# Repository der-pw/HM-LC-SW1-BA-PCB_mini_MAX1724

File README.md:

# AskSin++ Batterieaktor mit MAX1724 Stepup

**HM-LC-SW1-BA-PCB_mini mit einer Ausgangsspannung von 3,3V, bspw. für Mini-Lichterketten.**

* [Sketch](./Sketch/HM-LC-SW1-BA-PCB_extBatt.ino)
* [Gehäuse](./Case/)
* [Teileliste](./HM-LC-SW1-BA-PCB_mini_MAX1724-Parts.csv)

Der Ausgang wird über einen N-Channel MOSFET geschaltet und kann, je nach Versorgungsspannung, mit bis zu 150mA belastet werden.
Für kleine Mini-Lichterketten ist das ausreichend.
(Beispiel: eine Mini-Lichterkette aus den üblichen Grabbelschütten, mit 10 LEDs und 10Ohm Vorwiderstand benötigt ca 35mA).

**Batterie-Messung:**  
Desweiteren kann die Batteriespannung vor dem Stepup mittels Spannungsteiler gemessen werden. 
Ein angepasster Sketch liegt bei. Vielen Dank an Jérôme für die Unterstützung und das Aufzeigen, wie "einfach" doch die Batterieklasse ist. ;-)

Da in der CCU, bei diesem Aktor, die Batteriemeldung nur im Bereich von 5-15V auslöst, wird im Sketch unter ...
```
uint8_t lowbat = getList0().lowBatLimit() / 5; //factor 5 to get low bat
```
... die eingestellte Batterieschwelle durch 5 geteilt.
In der CCU müssen also die Spannungwerte mit "x5" angegeben werden.
Beispiel: Batteriemeldung bei 2,1V Versorgungsspannung. Heißt 2,1V x 5 = 10,5V. Es müssen demnach 10,5V in der CCU eingestellt werden.
Die Werte variieren je nach verwendetem Batterie.- Akkutyp und müssen "für sich selbst" gefunden werden.

## PCB

Das Platinendesign basiert auf dem [HMSensor](https://github.com/pa-pa/HMSensor/) Projekt.
Weitere Infos zur HMSensor gibt es auf [asksinpp.de](https://asksinpp.de/Projekte/psi/HMSensor/).

## FAQ

* `fatal error: ResetOnBoot.h: No such file or directory`  
  Es ist die aktuellste Version (ggf. master-Branch) der [AskSinPP](https://github.com/pa-pa/AskSinPP) Library zu verwenden

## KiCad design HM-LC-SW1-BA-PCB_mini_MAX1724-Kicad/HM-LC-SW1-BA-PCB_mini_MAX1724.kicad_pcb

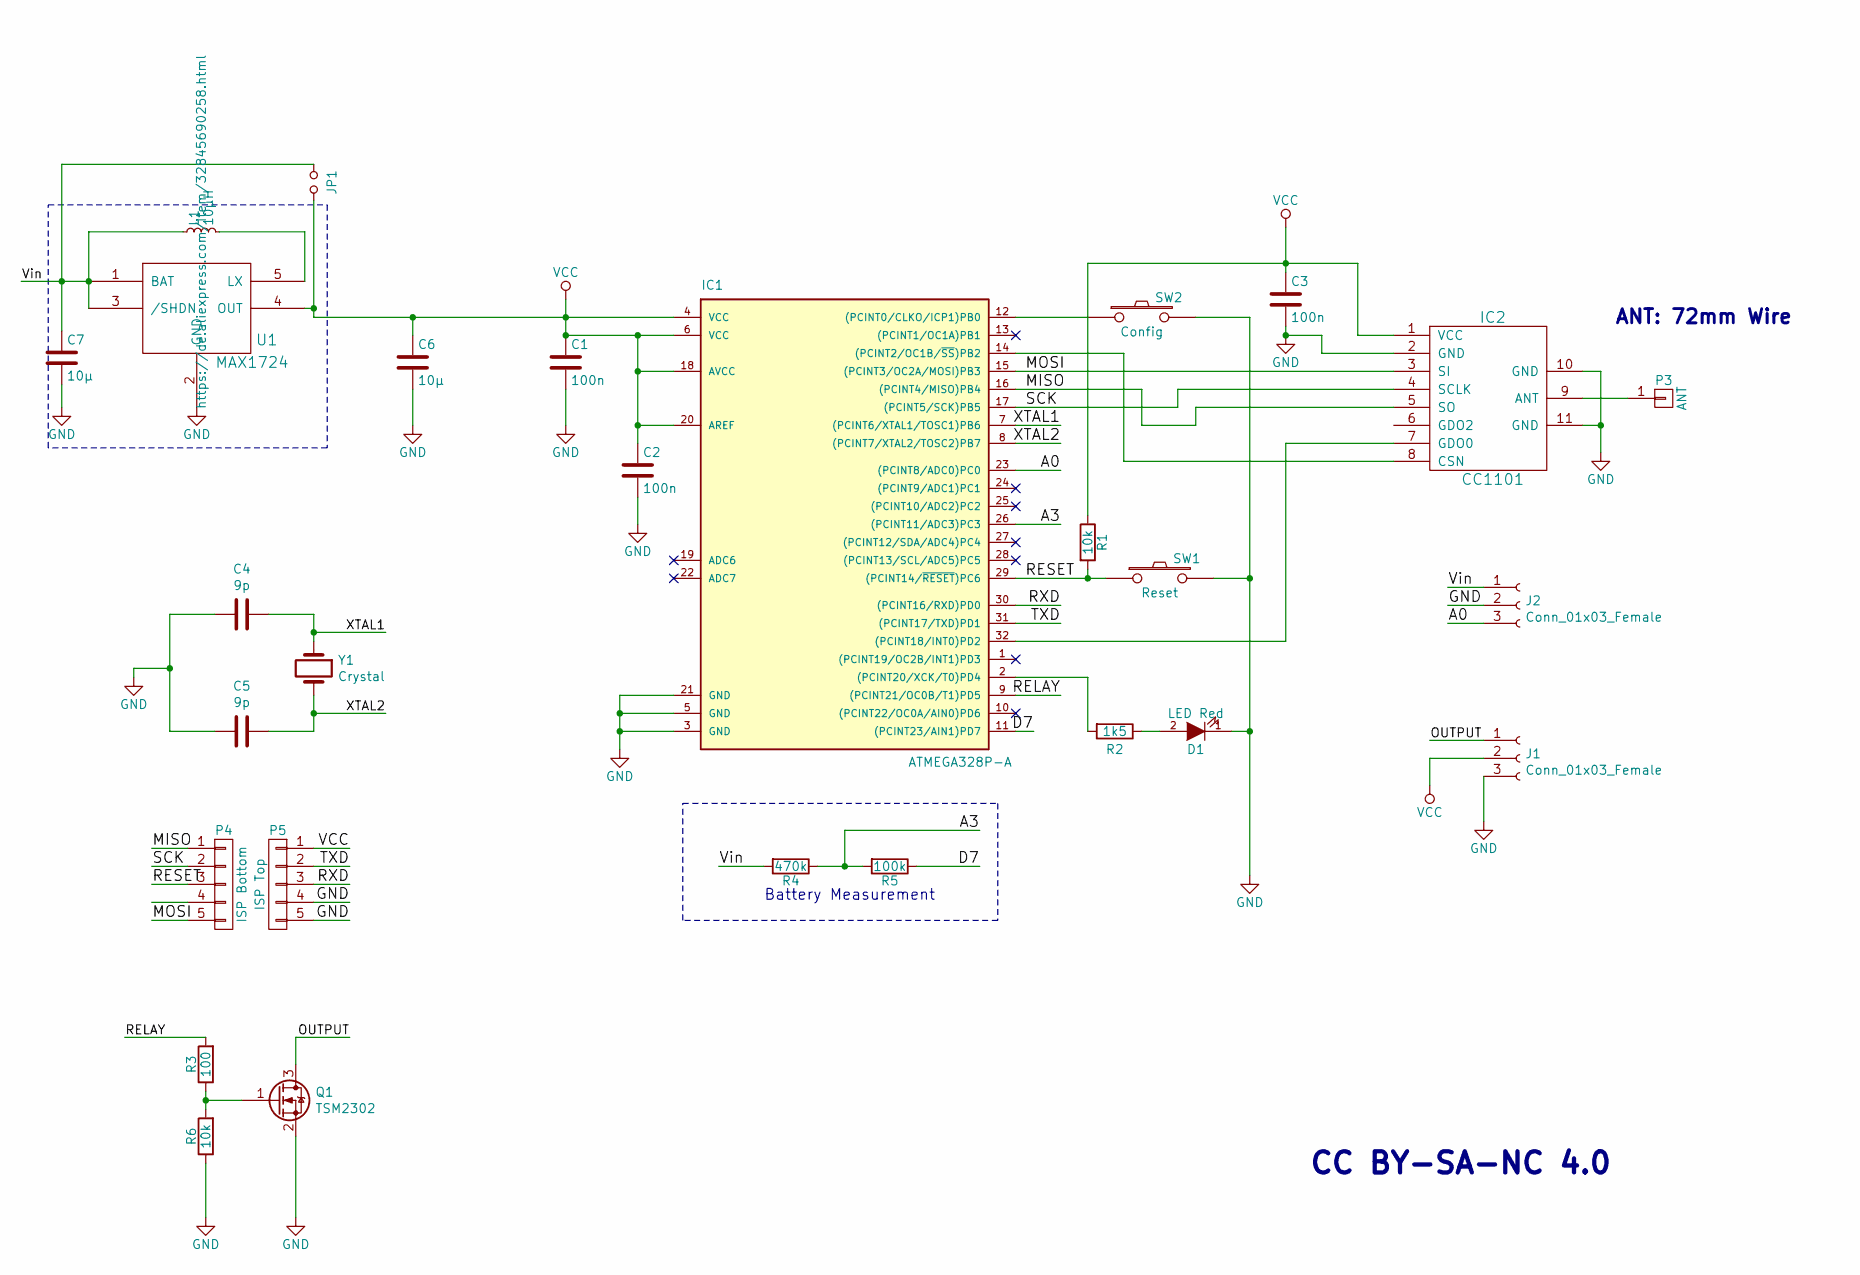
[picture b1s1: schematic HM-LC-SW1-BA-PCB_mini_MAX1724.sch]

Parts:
C1, C2, C3: 100n; C_0805_2012Metric_Pad1.15x1.40mm_HandSolder
C4, C5: 9p; C_0805_2012Metric_Pad1.15x1.40mm_HandSolder
C6, C7: 10µ; C_0805_2012Metric_Pad1.15x1.40mm_HandSolder
D1: LED Red; LED_1206_3216Metric_Pad1.42x1.75mm_HandSolder
IC1: ATMEGA328P-A; TQFP-32_7x7mm_Pitch0.8mm
IC2: CC1101; CC1101_Module
J1, J2: Conn_01x03_Female; PinHeader_1x03_P2.54mm_Vertical
JP1: Jumper_NO_Small; SolderJumper-2_P1.3mm_Open_RoundedPad1.0x1.5mm
L1: 10µH; L_1812_4532Metric_Pad1.30x3.40mm_HandSolder
P3: ANT; Pin_Header_Straight_1x01_Pitch2.00mm
P4: ISP Bottom; Pin_Header_Straight_1x05_Pitch2.54mm_SMD_BySide
P5: ISP Top; Pin_Header_Straight_1x05_Pitch2.54mm_SMD_BySide
Q1: TSM2302; SOT-23
R1: 10k; R_0805_HandSoldering
R2: 1k5; R_0805_2012Metric_Pad1.15x1.40mm_HandSolder
R3: 100; R_0805_2012Metric_Pad1.15x1.40mm_HandSolder
R4: 470k; R_0805_HandSoldering
R5: 100k; R_0805_HandSoldering
R6: 10k; R_0805_2012Metric_Pad1.15x1.40mm_HandSolder
SW1: Reset; SW_SPST_FSMSM
SW2: Config; SW_SPST_FSMSM
U1: MAX1724; TSOT-23-5
Y1: Crystal; Crystal_SMD_MicroCrystal_CC7V-T1A-2Pin_3.2x1.5mm_HandSolder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

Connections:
/A0: IC1.23 ((PCINT8/ADC0)PC0), J2.3
/A3: IC1.26 ((PCINT11/ADC3)PC3), R4.1, R5.2
/D7: IC1.11 ((PCINT23/AIN1)PD7), R5.1
/MISO: IC1.16 ((PCINT4/MISO)PB4), IC2.5 (SO), P4.1
/MOSI: IC1.15 ((PCINT3/OC2A/MOSI)PB3), IC2.3 (SI), P4.5
/OUTPUT: J1.1, Q1.3 (D)
/RELAY: IC1.9 ((PCINT21/OC0B/T1)PD5), R3.2
/RESET: IC1.29 ((PCINT14/~RESET~)PC6), P4.3, R1.2, SW1.1
/RXD: IC1.30 ((PCINT16/RXD)PD0), P5.3
/SCK: IC1.17 ((PCINT5/SCK)PB5), IC2.4 (SCLK), P4.2
/TXD: IC1.31 ((PCINT17/TXD)PD1), P5.2
/Vin: C7.1, J2.1, JP1.1, L1.1, R4.2, U1.1 (BAT), U1.3 (/SHDN)
/XTAL1: C4.1, IC1.7 ((PCINT6/XTAL1/TOSC1)PB6), Y1.1
/XTAL2: C5.1, IC1.8 ((PCINT7/XTAL2/TOSC2)PB7), Y1.2
GND: C1.2, C2.2, C3.2, C4.2, C5.2, C6.2, C7.2, D1.1 (K), IC1.3 (GND), IC1.5 (GND), IC1.21 (GND), IC2.2 (GND), IC2.10 (GND), IC2.11 (GND), J1.3, J2.2, P5.4, P5.5, Q1.2 (S), R6.1, SW1.2, SW2.2, U1.2 (GND)
unnamed: D1.2 (A), R2.1
unnamed: IC1.2 ((PCINT20/XCK/T0)PD4), R2.2
unnamed: IC1.12 ((PCINT0/CLKO/ICP1)PB0), SW2.1
unnamed: IC1.14 ((PCINT2/OC1B/~SS~)PB2), IC2.8 (CSN)
unnamed: IC1.32 ((PCINT18/INT0)PD2), IC2.7 (GDO0)
unnamed: IC2.9 (ANT), P3.1
unnamed: L1.2, U1.5 (LX)
unnamed: Q1.1 (G), R3.1, R6.2
VCC: C1.1, C2.1, C3.1, C6.1, IC1.4 (VCC), IC1.6 (VCC), IC1.18 (AVCC), IC1.20 (AREF), IC2.1 (VCC), J1.2, JP1.2, P5.1, R1.1, U1.4 (OUT)

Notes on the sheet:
Battery Measurement
CC BY-SA-NC 4.0
ANT: 72mm Wire

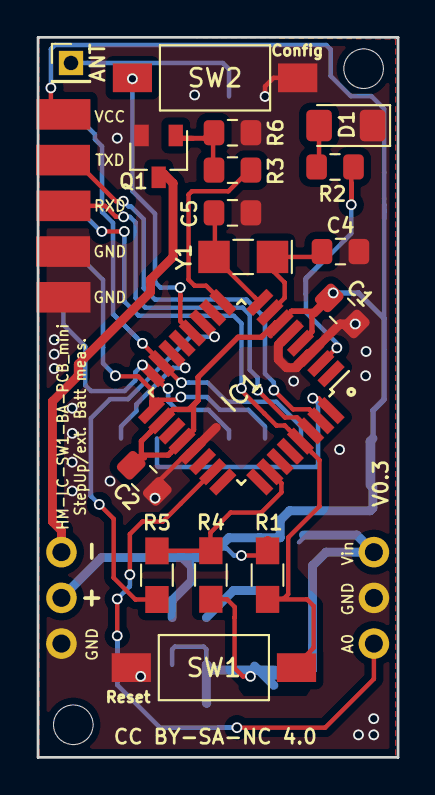
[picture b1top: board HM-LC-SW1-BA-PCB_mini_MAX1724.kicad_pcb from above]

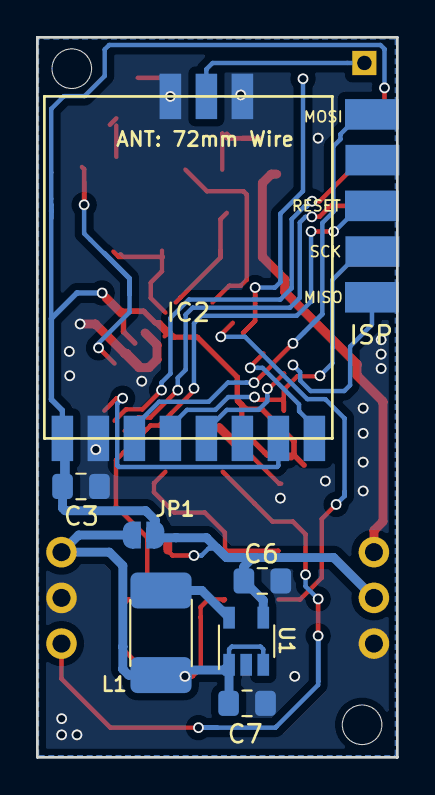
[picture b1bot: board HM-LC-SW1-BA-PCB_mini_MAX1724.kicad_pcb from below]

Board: 2 copper layers, 20.0 x 40.0 mm, 28 parts (8 on the bottom side), 24 nets.

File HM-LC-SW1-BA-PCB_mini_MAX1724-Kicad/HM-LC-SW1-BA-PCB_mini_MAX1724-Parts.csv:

Reference, Quantity, Value, Footprint, Datasheet
C1 C2 C3 ,3,"100n","Capacitor_SMD:C_0805_2012Metric_Pad1.15x1.40mm_HandSolder",""
C4 C5 ,2,"9p","Capacitor_SMD:C_0805_2012Metric_Pad1.15x1.40mm_HandSolder","~"
C6 C7 ,2,"10µ","Capacitor_SMD:C_0805_2012Metric_Pad1.15x1.40mm_HandSolder",""
D1 ,1,"LED Red","LED_SMD:LED_1206_3216Metric_Pad1.42x1.75mm_HandSolder",""
IC1 ,1,"ATMEGA328P-A","Housings_QFP:TQFP-32_7x7mm_Pitch0.8mm",""
IC2 ,1,"CC1101","Modules:CC1101_Module",""
J2 J1 ,2,"Conn_01x03_Female","Connector_PinHeader_2.54mm:PinHeader_1x03_P2.54mm_Vertical","~"
JP1 ,1,"Jumper_NO_Small","Jumper:SolderJumper-2_P1.3mm_Open_RoundedPad1.0x1.5mm",""
L1 ,1,"10µH","Inductor_SMD:L_1812_4532Metric_Pad1.30x3.40mm_HandSolder","https://de.aliexpress.com/item/32845690258.html"
P3 ,1,"ANT","Pin_Headers:Pin_Header_Straight_1x01_Pitch2.00mm",""
P4 ,1,"ISP Bottom","Modules:Pin_Header_Straight_1x05_Pitch2.54mm_SMD_BySide",""
P5 ,1,"ISP Top","Modules:Pin_Header_Straight_1x05_Pitch2.54mm_SMD_BySide",""
Q1 ,1,"TSM2302","Package_TO_SOT_SMD:SOT-23","http://www.farnell.com/datasheets/1945672.pdf"
R1 ,1,"10k","Resistors_SMD:R_0805_HandSoldering",""
R2 ,1,"1k5","Resistor_SMD:R_0805_2012Metric_Pad1.15x1.40mm_HandSolder",""
R3 ,1,"100","Resistor_SMD:R_0805_2012Metric_Pad1.15x1.40mm_HandSolder",""
R4 ,1,"470k","Resistors_SMD:R_0805_HandSoldering",""
R5 ,1,"100k","Resistors_SMD:R_0805_HandSoldering",""
R6 ,1,"10k","Resistor_SMD:R_0805_2012Metric_Pad1.15x1.40mm_HandSolder",""
SW1 ,1,"Reset","Buttons_Switches_SMD:SW_SPST_FSMSM",""
SW2 ,1,"Config","Buttons_Switches_SMD:SW_SPST_FSMSM",""
U1 ,1,"MAX1724","Package_TO_SOT_SMD:TSOT-23-5","https://de.aliexpress.com/item/32353066414.html"
Y1 ,1,"Crystal","Crystal:Crystal_SMD_MicroCrystal_CC7V-T1A-2Pin_3.2x1.5mm_HandSoldering","https://www.reichelt.de/uhrenquarz-keramikgeh-1-5x3-2x0-9mm-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"

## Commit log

2019-11-23 initial
2019-11-23 gerber upload
2019-11-23 order structure
2019-11-23 upload parts table
2019-11-23 Gehaeuse
2019-11-24 change footprint for L1
2019-11-24 add Panel 2x4
2019-11-25 change Relay to D5
    for further PWM options
2019-11-25 update pcb pics
2019-11-25 add V0.2 Panel
2019-12-05 update to V0.3
    improvement GND area inductor
2019-12-05 V0.3
    some small fixes
2019-12-09 panelize
    try an older Version of pcb panilzer
2019-12-09 panelize
2019-12-09 rename

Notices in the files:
README.md:
License: CC BY-NC-SA 4.0
